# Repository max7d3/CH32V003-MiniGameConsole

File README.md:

# CH32V003 Mini Game Console

## Introduction
Hi! I present to you a little project I have been working on... honestly, for a few years (on and off). But it's finally finished! This Mini Game Console uses one of the cheapest MCUs available, the CH32V003 (chosen when the project began in mid-2023), paired with also one of the cheapest color LCD display featuring a mind-blowing 80x160 resolution.

Despite memory limitations, it runs games with full 16-bit color\* graphics at 30 FPS (It can technically hit 60 FPS in all example games, but I designed them for 30, so I locked it there.) It supports either terminal grid and sprite graphics, has simple sound system and even option to save high score data.

It has simple "*game engine*" and each game can be kind of treated as independent program. There is API for buttons, sound and graphics, but it's all low-level anyways, so making games still require some knowledge how it all works overall.

Advanced game like Dino Run takes about ~2 kB in code alone. But for simple one like snake it's around 0.5 kB. With the example games and lto enabled there is about 1 kB of FLASH memory left, as well there are two free GPIOs. I didn't have idea what else to add despite e.g. flashlight functionality, but the project still can be expanded.

\**Single sprite can have 3 colors + transparency, but every sprite can use different palette.*

## Specifications
- **MCU:** CH32V003F4P6 (16 kB FLASH, 2 kB RAM, 48 MHz RISC-V)
- **Display:** ST7735 80x160 IPS LCD (SPI)
- **Audio:** PWM Buzzer
- **Input:** 5 Buttons
- **Current Games:**
    * Snake
    * Pong
    * Jump Bird
    * Dino Run
- **Other Features:**
    * High Score Saving
    * Flashlight Mode
    * Low Battery Detection

## Showcase Video

---

## Detailed Overview
Below I described the most important functionalities in more detail.

### Graphics System (`termGFX`)
Obviously, there is no way to fit a full frame buffer for this LCD into the MCU's available RAM. To solve this, graphics rendering is based on 8x8 blocks, and the main mode of operation is simple terminal-like graphics.

#### Terminal Graphics
Instead of storing whole picture in the memory, MCU uses map of chars and their color on the grid. Each block contains 2 bytes of information: character, 4-bit background color, 4-bit foreground color. On 80x160 display there are 200 blocks, so whole "frame buffer" for terminal uses 400 bytes of memory.

However, the buffer cannot be send to the LCD in format like that. That's why next step is rendering each block into little 8x8 frame buffer and drawing it on the screen in the right position. Rendering function checks which character to draw and in which colors, then renders the bitmap in the output buffer. Next the buffer is send to the LCD. 

That's the simple version. To achieve the higher frame rate there are further optimizations.

First, there is a map of 'dirty' blocks. An array of variables that act as bit fields, where '1' means change and '0' means lack of changes. All the exposed drawing functions write into that map. When the `tGFX_Update` is called to send the frame to LCD, the rendering function reads the map and skip all the blocks that didn't change. It also resets state of all the drawed blocks to '0'.

Second, the DMA of MCU is utilized to send data to LCD. And when data is being send to the LCD over SPI, the CPU switches output buffer and begin to render the next block. So we trade x2 RAM usage for almost x2 throughput increase.

Overall the terminal graphics in used configuration uses ~700 bytes of RAM. The usage can be further decreased by e.g. using only B/W colors. It can be also increased if we want more colors of text. But in this project I decided on compromise of 4-bit foreground/background colors of text.

This mode can be already used to make simple games. The Snake game implementation uses only this grid terminal graphics and custom characters. But for other games the 'free' graphics is needed, something that doesn't need to be aligned with the grid.

#### Sprite Graphics
Sprite system is based on map similar to the map of blocks to update. This time however, the '1' means block containing sprite. That's the simple part. From there it gets a bit complicated (at least in code), but the overall idea is pretty straightforward.

First step, or more like, step zero: sprites allocation. The code requires to know how many sprites are used, as well as information about them: position, size and color palette. Because when step one occurs and the block with sprite is processed, first thing that code does is iterating through all the allocated sprites and checking which one, and which part of it is on the current block.

When it finds out everything, the next step is rendering the sprite. To save memory, the sprites are encoded using 2-bit colors, so there is a bit of bit shuffling to decode them. The real colors are taken from palette attached to the sprite descriptor. Because color 0 is transparency, there are only 3 colors per sprite. But because of transparency, many sprites can be stacked on each other to achieve more colors.

And that's it. The efficiency of this solution heavily depends on what sprites and how many of them are used. If sprites are very large, probably stacking three or four on each other would make it... Well, maybe not so much lagging as just weird to look at, because of the block based rendering. With very small sprites, we can use a lot more, but sooner or later the boundary checking loop with o(n) complexity would become a problem.

There is probably a way to make it better, but it works fine for the games I wanted to make.

### The "*game engine*"
Calling this a 'game engine' might be a bit of an exaggeration. In reality, `engine.c` is primarily a system that manages function callbacks via a timer. It allows the current running 'program' (game) to be switched by simply changing the callback.

The current running 'program' is changed by changing the callback.

It also contains the common 512 bytes of memory that all the games share. A simple array that allows for simple dynamic allocation. The whole system is minimal, basically game can only allocate bytes, check how much memory is left, and clear it all.

### Menu

The main menu simply changes the engine callback to the entry point of selected game/utility. Besides displaying the list of games, it also displays a low-battery warning in the footer. It can also toggle sound generation.

Going back to the main menu is a matter of changing the callback back to main menu main function. And that entirely depends on whichever 'program' is being executed right now.

### Games
Each game act as indepent program with its own setup function and loop function. Every game has also struct `gs` (game state) that holds all the variables. The struct is actually a pointer mapped on the common memory pool. So, each game uses only 4 bytes of statick RAM for this pointer.

When I'm looking at this system now, it could be done better. Everything could just happen on stack. But it works, and I wanted to finally call this project  finished, so I left it like that.

I made four example games listed below:

#### Snake

#### Pong

#### Jump Bird (Flappy Bird clone)

#### Dino Run ("No Internet" Chrome game)

For gameplay watch the video (1:12): https://youtu.be/mhWHda4XlT0?si=jpvWHffCmz2jvb9t&t=72

### Game Over Screen

To save memory, the game over screen is also a 'game' that gets turn on when the game is over. The game that was running can set which button brings back main menu, what score to display etc.

### High Scores System

The console has a persistent​ memory to save high scores in games. It utilizes last page of CH32V003 flash. The pages of memory are 64 bytes in size, so we don't have to sacrifice lot of internal storage for that functionality.

The memory can be wiped by user. The scores are obviously saved only if current score is higher than previous one in memory.

### Other
#### Sound
Sound is generated using PWM and buzzer. Game can either play single tone for specific amount of time, or use a buffer of frequency and time values that will play in sequence automatically.

#### Input
Buttons are debounced and reading of their state is based on pooling. Games can also read raw state of the GPIO inputs and don't wait for debaunced input.

#### Battery Level Reading
Battery level is measured using PVD peripheral, not ADC. So, console can only tell if voltage is low or not.

### Hardware
> [!CAUTION]
> I designed example PCB that you can see on all the pictures. I share it, however, some resistors values depend on parts that you would use (LEDs, charging current). Also I modified the PCB and schematic indempedly while working on the project, so some fixes might be required. **If you intend to build one please double check it!** 
> I designed it assuming Li-Po cell with build in protection. **DO NOT USE UNPROTECTED CELLS!**
> There is a minor symmetry issue in the design: the power switch is centered relative to the LCD's active area, not the PCB itself

### Code Compilation
> [!TIP]
> To build the MounRiver Studio project with the lto (Link Time Optmalization) enabled, you must use GCC 12. The GCC 8 selected by default is bugged (at least from my experience): it cuts out all interrupt functions and volatile variables.

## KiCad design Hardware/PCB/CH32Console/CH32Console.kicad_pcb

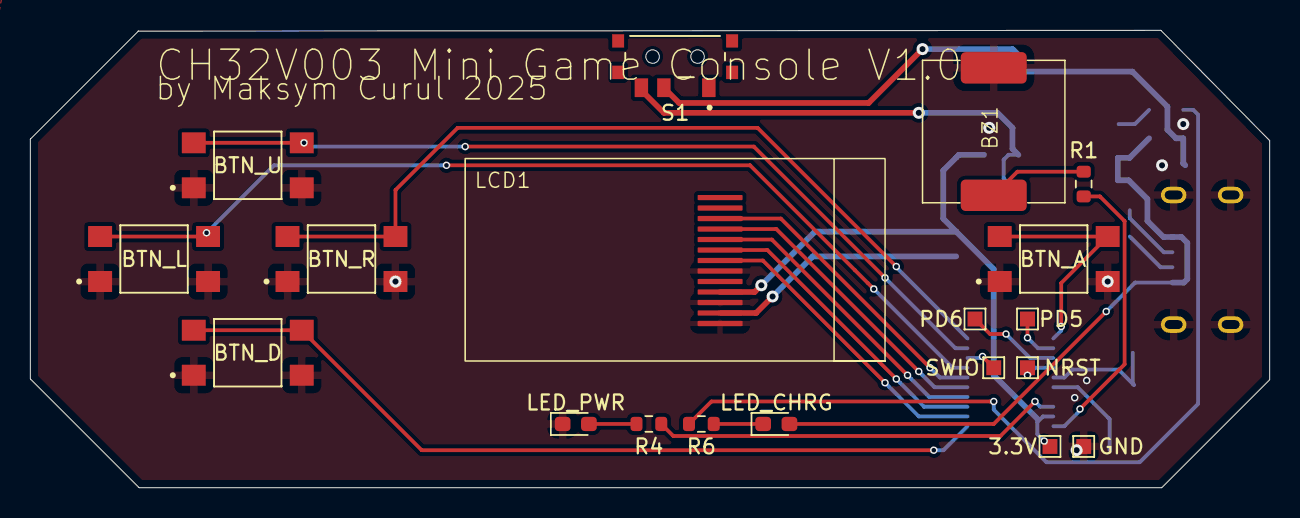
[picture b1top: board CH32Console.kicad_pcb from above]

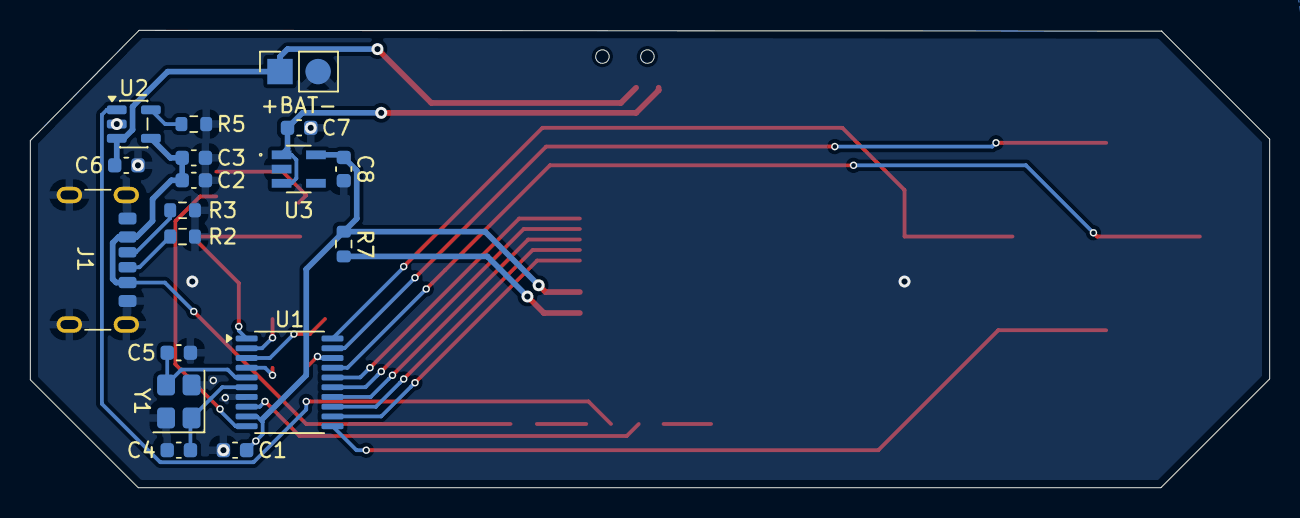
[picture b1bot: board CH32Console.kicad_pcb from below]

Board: 2 copper layers, 82.7 x 30.5 mm, 37 parts (18 on the bottom side), 31 nets.

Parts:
3.3V: Conn_01x01; TestPoint_Pad_1.0x1.0mm
+BAT-: BAT; PinSocket_1x02_P2.54mm_Vertical
BTN_A: TL3305AF160QG; SW_TL3305AF160QG
BTN_D: TL3305AF160QG; SW_TL3305AF160QG
BTN_L: TL3305AF160QG; SW_TL3305AF160QG
BTN_R: TL3305AF160QG; SW_TL3305AF160QG
BTN_U: TL3305AF160QG; SW_TL3305AF160QG
BZ1: Buzzer; buzz9mm
C1, C3: 100n; C_0603_1608Metric
C2, C6: 4.7u; C_0603_1608Metric
C4, C5: 10p; C_0603_1608Metric
C7: 1u; C_0603_1608Metric
C8: 2.2u; C_0603_1608Metric
GND: Conn_01x01; TestPoint_Pad_1.0x1.0mm
J1: USB_C_6P; USB_C_Receptacle_GCT_USB4125-xx-x-0190_6P_TopMnt_Horizontal
LCD1: ST7735; st7735_footprintv1
LED_CHRG: LED_CHRG; LED_0603_1608Metric_Pad1.05x0.95mm_HandSolder
LED_PWR: LED_PWR; LED_0603_1608Metric_Pad1.05x0.95mm_HandSolder
NRST: Conn_01x01; TestPoint_Pad_1.0x1.0mm
PD5, PD6: Conn_01x01; TestPoint_Pad_1.0x1.0mm
R1: R_buzz; R_0603_1608Metric
R2, R3: 5.1k; R_0603_1608Metric
R4: 220; R_0603_1608Metric
R5: R_prog; R_0603_1608Metric
R6: 470; R_0603_1608Metric
R7: R_lcd; R_0603_1608Metric
S1: SLW-66527511-SMT-TR; SW_SLW-66527511-SMT-TR
SWIO: Conn_01x01; TestPoint_Pad_1.0x1.0mm
U1: CH32V003FxPx; TSSOP-20_4.4x6.5mm_P0.65mm
U2: MCP73831-2-OT; SOT-23-5
U3: LD2980CM33TR; SOT95P280X145-5N
Y1: 24MHz; Crystal_SMD_3225-4Pin_3.2x2.5mm

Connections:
+3.3V: 3.3V.1, C1.1, C8.1, LCD1.10 (VCC), R7.1, U1.9 (VDD), U3.5 (VOUT)
BTN_ACTION: BTN_A.3, BTN_A.4, U1.1 (PD4)
BTN_DOWN: BTN_D.3, BTN_D.4, U1.11 (PC1)
BTN_LEFT: BTN_L.3, BTN_L.4, U1.17 (PC7)
BTN_RIGHT: BTN_R.3, BTN_R.4, U1.20 (PD3)
BTN_UP: BTN_U.3, BTN_U.4, U1.19 (PD2)
BUZZ: R1.1, U1.10 (PC0)
CS: LCD1.7 (CS), U1.12 (PC2)
DC: LCD1.5 (RS), U1.14 (PC4)
GND: +BAT-.2, BTN_A.1, BTN_A.2, BTN_D.1, BTN_D.2, BTN_L.1, BTN_L.2, BTN_R.1, BTN_R.2, BTN_U.1, BTN_U.2, BZ1.2 (-), C1.2, C2.2, C3.2, C4.2, C5.2, C6.2, C7.2, C8.2, GND.1, J1.A12 (GND), J1.B12 (GND), J1.S1 (SHIELD), LCD1.8 (GND), LCD1.11 (LEDK), LCD1.13 (GND), LED_PWR.1 (K), R2.2, R3.2, R5.1, U1.7 (VSS), U2.2 (V_{SS}), U3.2 (GND), Y1.2, Y1.4
MOSI: LCD1.3 (SDA), U1.16 (PC6)
NRST: NRST.1, U1.4 (PD7)
unnamed: +BAT-.1, C6.1, S1.2, U2.3 (V_{BAT})
unnamed: BZ1.1 (+), R1.2
unnamed: LED_PWR.2 (A), R4.2
unnamed: C2.1, C3.1, J1.A9 (VBUS), J1.B9 (VBUS), LED_CHRG.2 (A), U2.4 (V_{DD})
unnamed: LED_CHRG.1 (K), R6.2
unnamed: J1.A5 (CC1), R3.1
unnamed: J1.B5 (CC2), R2.1
unnamed: LCD1.12 (LEDA), R7.2
unnamed: PD5.1, U1.2 (PD5)
unnamed: PD6.1, U1.3 (PD6)
unnamed: C5.1, U1.5 (PA1), Y1.3
unnamed: C4.1, U1.6 (PA2), Y1.1
unnamed: R4.1, U1.8 (PD0)
unnamed: R5.2, U2.5 (PROG)
unnamed: R6.1, U2.1 (STAT)
unnamed: C7.1, S1.3, U3.1 (VIN), U3.3 (INHIBIT)
RS: LCD1.6 (RES), U1.13 (PC3)
SCK: LCD1.4 (SCL), U1.15 (PC5)
SWIO: SWIO.1, U1.18 (PD1)

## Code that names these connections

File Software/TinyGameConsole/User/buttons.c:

/*
 * buttons.c
 *
 *  Created on: Jun 25, 2023
 *      Author: max
 */

#include <stdlib.h>

#include "debug.h"
#include "ch32v00x.h"
#include "tick.h"

#include "buttons.h"

/*
*					BUTTONS CONNECTIONS
*
*			PD2 -> UP
*
*	PC7 -> LEFT		PD3 -> RIGHT	PD4 -> ACTION
*			
*			PC1 -> DOWN
*
*/

volatile button_status_t BUTTONS[BTN_COUNT];

void BTN_Init(void)
{
	RCC->APB2PCENR |= RCC_APB2Periph_GPIOC | RCC_APB2Periph_GPIOD;

	// Clear previous configuration and set new one (input with pull resistors)
	GPIOC->CFGLR &= ~((0b11 << 30) | (0b11 << 6));
	GPIOC->CFGLR |= (0b10 << 30) | (0b10 << 6);

	// Clear previous configuration and set new one (input with pull resistors)
	GPIOD->CFGLR &= ~((0b11 << 10) | (0b11 << 14) | (0b11 << 18));
	GPIOD->CFGLR |= (0b10 << 10) | (0b10 << 14) | (0b10 << 18);

	// Enable pull-ups
	GPIOC->OUTDR |= (1 << 7) | (1 << 1);
	GPIOD->OUTDR |= (1 << 2) | (1 << 3) | (1 << 4);


}

static uint8_t _BTN_CheckState(buttons_names_t button)
{
    switch (button)
    {

        case BTN_ACTION:
        return (GPIOD->INDR >> 4) & 1;

        case BTN_RIGHT:
        return (GPIOD->INDR >> 3) & 1;

        case BTN_UP:
        return (GPIOD->INDR >> 2) & 1;

        case BTN_LEFT:
        return (GPIOC->INDR >> 7) & 1;

        case BTN_DOWN:
        return (GPIOC->INDR >> 1) & 1;

        default:
        return 0;

    }
}

void BTN_Task(void)
{
	for(size_t i = 0; i < BTN_COUNT; i++)
	{
		switch(BUTTONS[i].state)
		{
			case BTN_STATE_IDLE:

				if(_BTN_CheckState(i) == 0)
				{
					BUTTONS[i].state = BTN_STATE_DEBOUNCE;
					BUTTONS[i].last_tick = TICK_Get();
				}

				break;

			case BTN_STATE_DEBOUNCE:

				if ((TICK_Get() - BUTTONS[i].last_tick) > BTN_DEBOUNCE_TIME)
				{
					if (_BTN_CheckState(i) == 0)
					{
						BUTTONS[i].state = BTN_STATE_PRESSED;
					}
					else
					{
						BUTTONS[i].state = BTN_STATE_IDLE;
					}

				}

				break;

			case BTN_STATE_PRESSED:

				if (_BTN_CheckState(i) == 1)
				{
					BUTTONS[i].state = BTN_STATE_IDLE;
				}

				break;
		}
	}
}

uint8_t BTN_IsPressed(buttons_names_t button)
{
	if(BUTTONS[button].state == BTN_STATE_PRESSED) return 1;
	return 0;
}

uint8_t BTN_IsPressedRAW(buttons_names_t button)
{
	if(!_BTN_CheckState(button)) return 1;
	return 0;
}

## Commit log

2026-02-11 Change info box to tip and update GCC version note
    Updated note on code compilation to reflect GCC version change.
2026-02-11 Fix typos
